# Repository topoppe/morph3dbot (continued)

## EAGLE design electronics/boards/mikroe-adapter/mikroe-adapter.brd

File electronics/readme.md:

# *Morph3DBot*-Platinen

Alle Platinen für das *Morph3DBot* System haben den selben Formfaktor und werden auf die Basisstruktur montiert.
Die Platinen werden untereinander mit einem vierpoligen Kabel verbunden. Über dieses Kabel werden die Platinen mit Strom versorgt und können
miteinander kommunizieren.

Die Kommunikation erfolgt über einen I2C-Bus, die Spannungsversorgung bringt die Batteriespannung an alle Platinen.

Jede Platine hat mindestens 2 Stecker zum verbinden mit anderen Platinen. Dadurch kann die Verkabelung zu den einzelnen Modulen
als Daisy-Chain ausgeführt werden und wird wesentlich vereinfacht.
Bei den meisten Platinen lässt sich die I2C-Adresse entweder per Software oder per DIP-Schalter einstellen.

Bis jetzt gibt es bereits folgende Platinen:
- Stromversorgung: Diese Platine darf und muss genau einmal im System verbaut werden. Hier wird die Stromquelle wie z.B. eine Batterie oder ein Netzteil angeschlossen. Außerdem sind hier die Pull-Up-Widerstände für den I2C-Bus verbaut.
- HUB-Platine: Dient als Verteiler. Hier können bis zu 8 weitere Platinen angeschlossen werden
- AT-Mega-328-Platine: Diese Platine ist mit einem ATMega328p Controller bestückt. Sie kann als "Gehirn" des Systems verwendet werden
- ESP32-Platine: Diese Platine ist mit einem ESP32-Wroom-Modul bestückt. Auch sie kann als "Gehirn" verwendet werden, besitzt aber auch WLAN und Bluetooth Schnittstellen
- Taster-Platine: Sie besitzt 5 Taster um eingaben ins System zu ermöglichen
- Ultrasonic-Platine: Hier kann ein 4-poliger Ultraschall Sensor angeschlossen werden
- Motor-und-Servo-Platine: An dieser Platine können 8 Servos sowie 2 Gleichstrommotoren angeschlossen werden
- Servo-Platine: Wie die Motor-und-Servo-Platine, jedoch ohne die Anschlüsse für die Gleichstrommotoren
- Line-Follower-Platine: Mit ihr kann eine Linie auf dem Boden erkannt werden
- Mikroe-Platine: Hier kann ein "Click-Board" von Mikroe.com angeschlossen werden

Zusätzlich gibt es eine Platine mit einem anderen Formfaktor: Die "TT-Motor-Platine". Diese Platine kann direkt auf die aus dem Maker-Bereich bekannten TT-Motoren geklebt werden. Sie besitzt eine I2C-Schnittstelle, einen Motortreiber sowie Eingänge für den Enkoder des Motors. Angeschlossen wird die Platine mit dem selben System wie die restlichen *Morph3DBot* Platinen.

Für die ATMega, die ESP32- sowie für die Platinen mit ATTINY-Controller stehen Templates im Repo bereit. Alle Grundbauteile sind bereits vorhanden, sodass eigene Platinen schnell erstellt werden können.

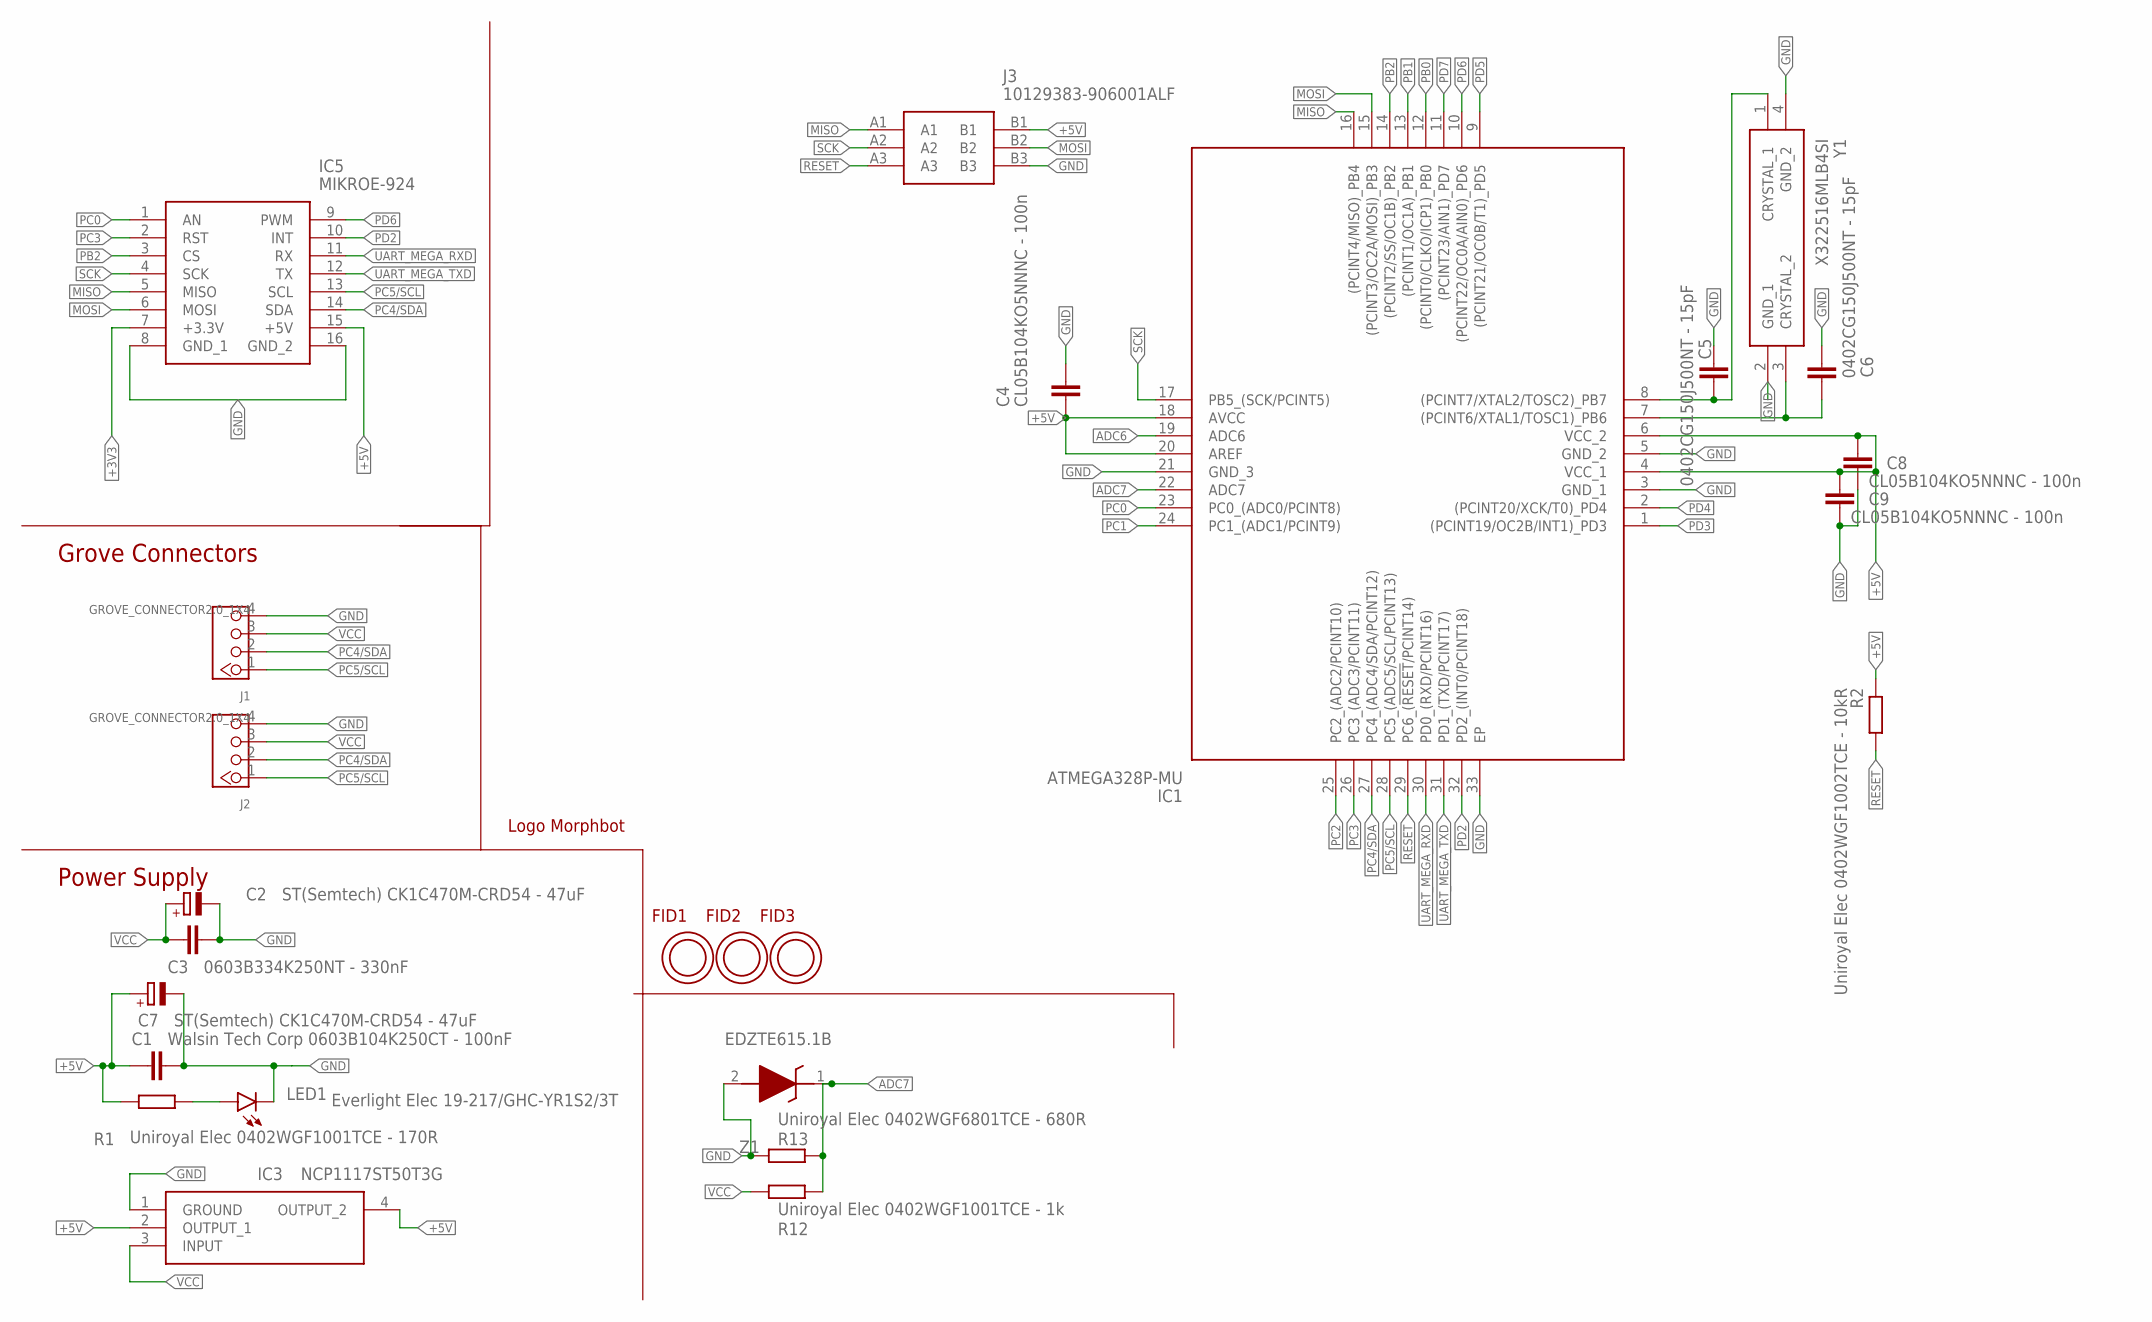
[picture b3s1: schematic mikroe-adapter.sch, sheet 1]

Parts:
C1: Walsin Tech Corp 0603B104K250CT - 100nF; C0603
C2, C7: ST(Semtech) CK1C470M-CRD54 - 47uF; PANASONIC_C
C3: 0603B334K250NT - 330nF; C0603
C4, C8, C9: CL05B104KO5NNNC - 100n; C0402
C5, C6: 0402CG150J500NT - 15pF; C0402
FID1, FID2, FID3: OPEN-PNP-FIDUCIAL
IC1: ATMEGA328P-MU; QFN50P500X500X100-33N
IC3: NCP1117ST50T3G; SOT230P700X180-4N
IC5: MIKROE-924; MIKROE924
J1, J2: GROVE_CONNECTOR2.0_1X4; 2.0_1X4_STRAIGHT
J3: 10129383-906001ALF; 10129383906001ALF
LED1: Everlight Elec 19-217/GHC-YR1S2/3T; CHIPLED_0603
R1: Uniroyal Elec 0402WGF1001TCE - 170R; R0402
R2: Uniroyal Elec 0402WGF1002TCE - 10kR; R0402
R12: Uniroyal Elec 0402WGF1001TCE - 1k; R0402
R13: Uniroyal Elec 0402WGF6801TCE - 680R; R0402
U$1: LOGO_MORPHBOT5MM; LOGO_MORPHBOT
Y1: X322516MLB4SI
Z1: EDZTE615.1B; EMD2

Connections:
+3V3: IC5.7 (+3.3V); also elsewhere on the board
+5V: C1.1, C4.1, C7.+, C8.2, C9.2, IC1.4 (VCC_1), IC1.6 (VCC_2), IC1.18 (AVCC), IC1.20 (AREF), IC3.2 (OUTPUT_1), IC3.4 (OUTPUT_2), IC5.15 (+5V), J3.B1, R1.2, R2.2; also elsewhere on the board
ADC6: IC1.19 (ADC6)
ADC7: IC1.22 (ADC7), R12.1, R13.2, Z1.1 (K)
GND: C1.2, C2.-, C3.1, C4.2, C5.1, C6.1, C7.-, C8.1, C9.1, IC1.3 (GND_1), IC1.5 (GND_2), IC1.21 (GND_3), IC1.33 (EP), IC3.1 (GROUND), IC5.8 (GND_1), IC5.16 (GND_2), J1.4, J2.4, J3.B3, LED1.C, R13.1, Y1.2 (GND_1), Y1.4 (GND_2), Z1.2 (A); also elsewhere on the board
MISO: IC1.16 ((PCINT4/MISO)_PB4), IC5.5 (MISO), J3.A1
MOSI: IC1.15 ((PCINT3/OC2A/MOSI)_PB3), IC5.6 (MOSI), J3.B2
unnamed: LED1.A, R1.1
unnamed: C5.2, IC1.8 ((PCINT7/XTAL2/TOSC2)_PB7), Y1.1 (CRYSTAL_1)
unnamed: C6.2, IC1.7 ((PCINT6/XTAL1/TOSC1)_PB6), Y1.3 (CRYSTAL_2)
PB0: IC1.12 ((PCINT0/CLKO/ICP1)_PB0)
PB1: IC1.13 ((PCINT1/OC1A)_PB1)
PB2: IC1.14 ((PCINT2/SS/OC1B)_PB2), IC5.3 (CS)
PC0: IC1.23 (PC0_(ADC0/PCINT8)), IC5.1 (AN)
PC1: IC1.24 (PC1_(ADC1/PCINT9))
PC2: IC1.25 (PC2_(ADC2/PCINT10))
PC3: IC1.26 (PC3_(ADC3/PCINT11)), IC5.2 (RST)
PC4/SDA: IC1.27 (PC4_(ADC4/SDA/PCINT12)), IC5.14 (SDA), J1.2, J2.2
PC5/SCL: IC1.28 (PC5_(ADC5/SCL/PCINT13)), IC5.13 (SCL), J1.1, J2.1
PD2: IC1.32 (PD2_(INT0/PCINT18)), IC5.10 (INT)
PD3: IC1.1 ((PCINT19/OC2B/INT1)_PD3)
PD4: IC1.2 ((PCINT20/XCK/T0)_PD4)
PD5: IC1.9 ((PCINT21/OC0B/T1)_PD5)
PD6: IC1.10 ((PCINT22/OC0A/AIN0)_PD6), IC5.9 (PWM)
PD7: IC1.11 ((PCINT23/AIN1)_PD7)
RESET: IC1.29 (PC6_(!RESET!/PCINT14)), J3.A3, R2.1; also elsewhere on the board
SCK: IC1.17 (PB5_(SCK/PCINT5)), IC5.4 (SCK), J3.A2
UART_MEGA_RXD: IC1.30 (PD0_(RXD/PCINT16)), IC5.11 (RX); also elsewhere on the board
UART_MEGA_TXD: IC1.31 (PD1_(TXD/PCINT17)), IC5.12 (TX); also elsewhere on the board
VCC: C2.+, C3.2, IC3.3 (INPUT), J1.3, J2.3, R12.2; also elsewhere on the board

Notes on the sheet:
Power Supply
Grove Connectors

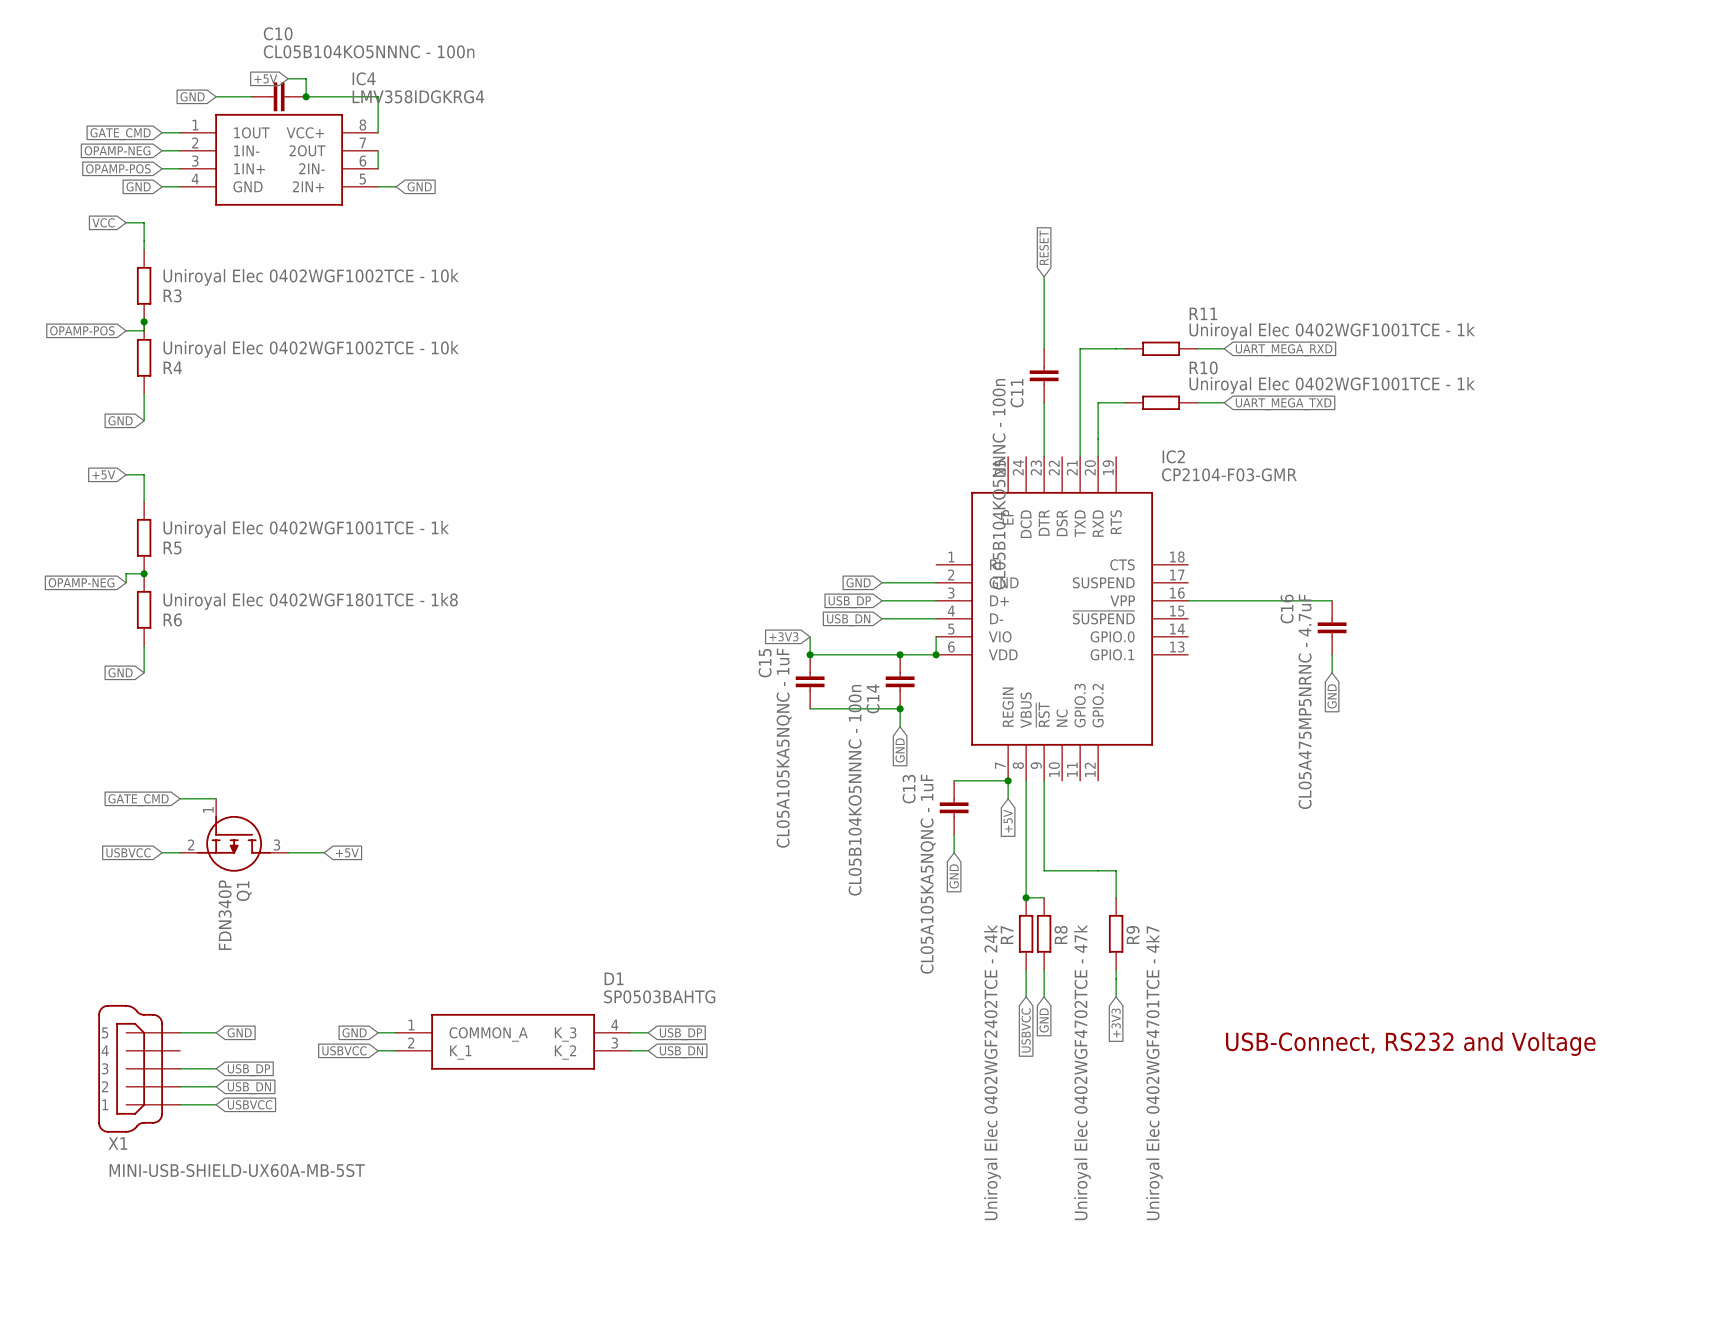
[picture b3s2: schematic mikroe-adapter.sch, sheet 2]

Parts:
C10, C11, C14: CL05B104KO5NNNC - 100n; C0402
C13, C15: CL05A105KA5NQNC - 1uF; C0402
C16: CL05A475MP5NRNC - 4.7uF; C0402
D1: SP0503BAHTG
IC2: CP2104-F03-GMR; QFN50P400X400X80-25N
IC4: LMV358IDGKRG4; SOP65P490X110-8N
Q1: FDN340P; SOT95P237X112-3N
R3, R4: Uniroyal Elec 0402WGF1002TCE - 10k; R0402
R5, R10, R11: Uniroyal Elec 0402WGF1001TCE - 1k; R0402
R6: Uniroyal Elec 0402WGF1801TCE - 1k8; R0402
R7: Uniroyal Elec 0402WGF2402TCE - 24k; R0402
R8: Uniroyal Elec 0402WGF4702TCE - 47k; R0402
R9: Uniroyal Elec 0402WGF4701TCE - 4k7; R0402
X1: MINI-USB-SHIELD-UX60A-MB-5ST; UX60A-MB-5ST

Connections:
+3V3: C14.2, C15.2, IC2.5 (VIO), IC2.6 (VDD), R9.2; also elsewhere on the board
+5V: C10.2, C13.2, IC2.7 (REGIN), IC4.8 (VCC+), Q1.3 (D), R5.1; also elsewhere on the board
DTR: C11.1, IC2.23 (DTR)
GATE_CMD: IC4.1 (1OUT), Q1.1 (G)
GND: C10.1, C13.1, C14.1, C15.1, C16.1, D1.1 (COMMON_A), IC2.2 (GND), IC4.4 (GND), IC4.5 (2IN+), R4.2, R6.2, R8.2, X1.5; also elsewhere on the board
unnamed: IC4.6 (2IN-), IC4.7 (2OUT)
unnamed: IC2.8 (VBUS), R7.1, R8.1
unnamed: IC2.9 (!RST), R9.1
unnamed: C16.2, IC2.16 (VPP)
unnamed: IC2.21 (TXD), R11.1
unnamed: IC2.20 (RXD), R10.1
OPAMP-NEG: IC4.2 (1IN-), R5.2, R6.1
OPAMP-POS: IC4.3 (1IN+), R3.2, R4.1
RESET: C11.2; also elsewhere on the board
UART_MEGA_RXD: R11.2; also elsewhere on the board
UART_MEGA_TXD: R10.2; also elsewhere on the board
USBVCC: D1.2 (K_1), Q1.2 (S), R7.2, X1.1
USB_DN: D1.3 (K_2), IC2.4 (D-), X1.2
USB_DP: D1.4 (K_3), IC2.3 (D+), X1.3
VCC: R3.1; also elsewhere on the board

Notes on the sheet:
USB-Connect, RS232 and Voltage

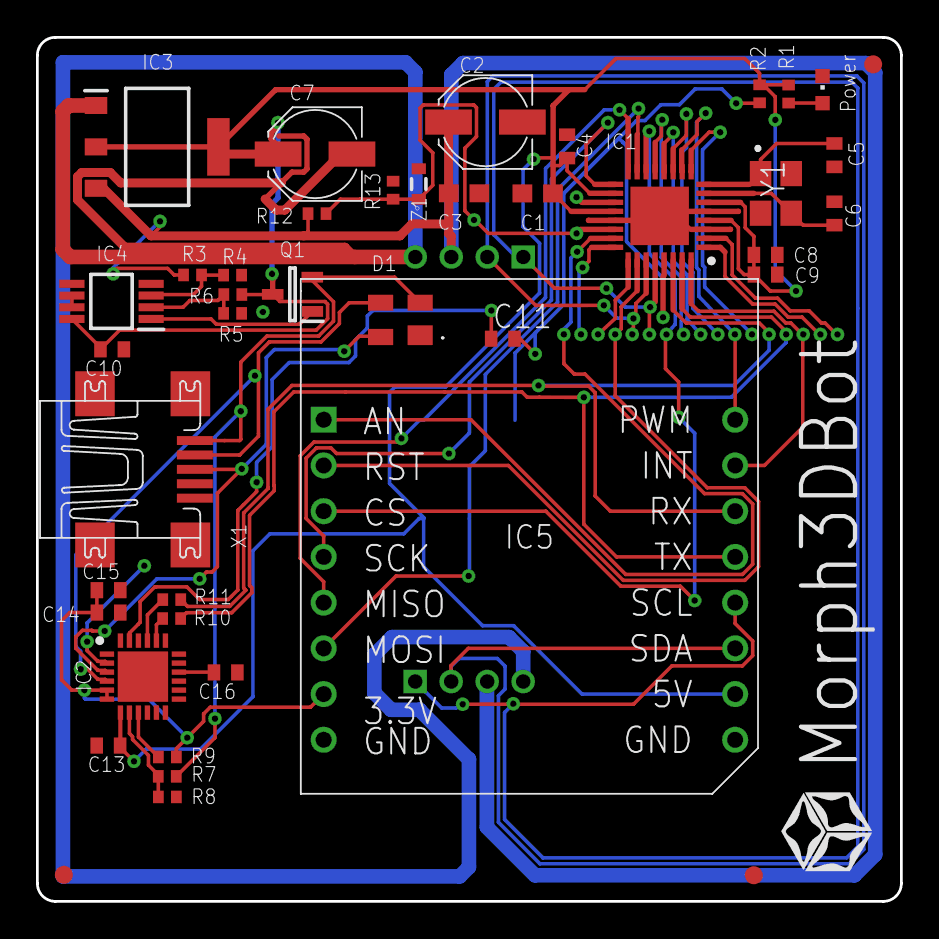
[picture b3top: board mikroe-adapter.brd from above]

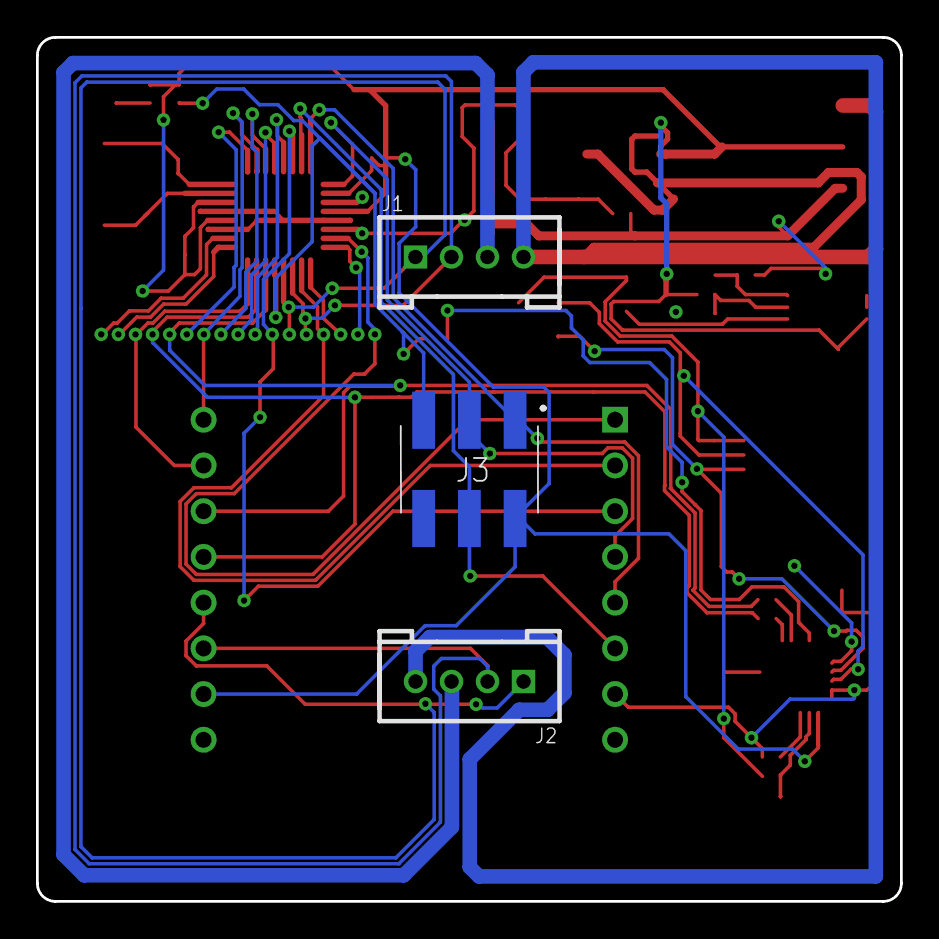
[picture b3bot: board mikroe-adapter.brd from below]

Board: 2 copper layers, 48.0 x 48.0 mm, 46 parts (3 on the bottom side), 34 nets.

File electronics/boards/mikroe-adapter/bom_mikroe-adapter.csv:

"Qty";"Value";"Device";"Package";"Parts";"Description";"ARROW_PART_NUMBER";"ARROW_PRICE-STOCK";"DESCRIPTION";"HEIGHT";"MANUFACTURER_NAME";"MANUFACTURER_PART_NUMBER";"MF";"MOUSER_PART_NUMBER";"MOUSER_PRICE-STOCK";"MPN";"OC_FARNELL";"OC_NEWARK";"POPULARITY";"SPICEPREFIX";
"2";"0402CG150J500NT - 15pF";"C-EUC0402";"C0402";"C5, C6";"CAPACITOR, European symbol";"";"";"";"";"";"";"";"";"";"";"";"";"18";"C";
"1";"0603B334K250NT - 330nF";"C-EUC0603";"C0603";"C3";"CAPACITOR, European symbol";"";"";"";"";"";"";"";"";"";"";"";"";"73";"C";
"1";"10129383-906001ALF";"10129383-906001ALF";"10129383906001ALF";"J3";"Headers & Wire Housings ECONOSTIK HEADER DR VT SMT 2X3";"10129383-906001ALF";"https://www.arrow.com/en/products/10129383-906001alf/amphenol-fci";"Headers & Wire Housings ECONOSTIK HEADER DR VT SMT 2X3";"8.58mm";"Amphenol";"10129383-906001ALF";"";"649-1012938390601ALF";"https://www.mouser.co.uk/ProductDetail/Amphenol-FCI/10129383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";"";"";"";"";"";
"1";"ATMEGA328P-MU";"ATMEGA328P-MU";"QFN50P500X500X100-33N";"IC1";"ATMEGA328P-MU, 8 bit AVR Microcontroller 20MHz 1, 32kb Flash, 2kb RAM, I2C SPI 32-Pin MLF";"ATMEGA328P-MU";"https://www.arrow.com/en/products/atmega328p-mu/microchip-te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";"ATMEGA328P-MU, 8 bit AVR Microcontroller 20MHz 1, 32kb Flash, 2kb RAM, I2C SPI 32-Pin MLF";"1mm";"Microchip";"ATMEGA328P-MU";"";"556-ATMEGA328P-MU";"https://www.mouser.co.uk/ProductDetail/Microchip-Technology-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";"";"";"";"";"";
"2";"CL05A105KA5NQNC - 1uF";"C-EUC0402";"C0402";"C13, C15";"CAPACITOR, European symbol";"";"";"";"";"";"";"";"";"";"";"";"";"18";"C";
"1";"CL05A475MP5NRNC - 4.7uF";"C-EUC0402";"C0402";"C16";"CAPACITOR, European symbol";"";"";"";"";"";"";"";"";"";"";"";"";"18";"C";
"6";"CL05B104KO5NNNC - 100n";"C-EUC0402";"C0402";"C4, C8, C9, C10, C11, C14";"CAPACITOR, European symbol";"";"";"";"";"";"";"";"";"";"";"";"";"18";"C";
"1";"CP2104-F03-GMR";"CP2104-F03-GMR";"QFN50P400X400X80-25N";"IC2";"USB-to-UART 1-CH 576byte FIFO 3.3V Automotive 24-Pin QFN EP T/R";"CP2104-F03-GMR";"https://www.arrow.com/en/products/cp2104-f03-gmr/silicon-labs";"USB-to-UART 1-CH 576byte FIFO 3.3V Automotive 24-Pin QFN EP T/R";"0.8mm";"Silicon Labs";"CP2104-F03-GMR";"";"634-CP2104-F03-GMR";"https://www.mouser.co.uk/ProductDetail/Silicon-Labs/CP2104-F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";"";"";"";"";"";
"1";"EDZTE615.1B";"EDZTE615.1B";"EMD2";"Z1";"ROHM EDZTE615.1B Zener Diode, 5.1V 2% 0.1 W SMT 2-Pin EMD";"";"";"ROHM EDZTE615.1B Zener Diode, 5.1V 2% 0.1 W SMT 2-Pin EMD";"mm";"ROHM Semiconductor";"EDZTE615.1B";"";"755-EDZTE615.1B";"https://www.mouser.co.uk/ProductDetail/ROHM-Semiconductor/ED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";"";"";"";"";"";
"1";"Everlight Elec 19-217/GHC-YR1S2/3T";"LEDCHIPLED_0603";"CHIPLED_0603";"LED1";"LED";"";"";"";"";"";"";"";"";"";"";"";"";"28";"";
"1";"FDN340P";"FDN340P";"SOT95P237X112-3N";"Q1";"Trans MOSFET P-CH 20V 2A 3-Pin SuperSOT";"FDN340P";"https://www.arrow.com/en/products/fdn340p/on-semiconductor";"Trans MOSFET P-CH 20V 2A 3-Pin SuperSOT";"1.12mm";"ON Semiconductor";"FDN340P";"";"512-FDN340P";"https://www.mouser.co.uk/ProductDetail/ON-Semiconductor-Fair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";"";"";"";"";"";
"2";"GROVE_CONNECTOR2.0_1X4";"GROVE_CONNECTOR2.0_1X4";"2.0_1X4_STRAIGHT";"J1, J2";"Seeedstudio Grove-Connector:";"";"";"";"";"";"";"";"";"";"";"";"";"";"";
"1";"LMV358IDGKRG4";"LMV358IDGKRG4";"SOP65P490X110-8N";"IC4";"Operational Amplifiers - Op Amps Dual Low-Voltage Rail-to-Rail Out";"LMV358IDGKRG4";"https://www.arrow.com/en/products/lmv358idgkrg4/texas-instruments";"Operational Amplifiers - Op Amps Dual Low-Voltage Rail-to-Rail Out";"1.1mm";"Texas Instruments";"LMV358IDGKRG4";"";"595-LMV358IDGKRG4";"https://www.mouser.co.uk/ProductDetail/Texas-Instruments/LMV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";"";"";"";"";"";
"1";"LOGO_MORPHBOT5MM";"LOGO_MORPHBOT5MM";"LOGO_MORPHBOT";"U$1";"";"";"";"";"";"";"";"";"";"";"";"";"";"";"";
"1";"MIKROE-924";"MIKROE-924";"MIKROE924";"IC5";"microSD click mikroBUS";"";"";"microSD click mikroBUS";"5mm";"MIKROELEKTRONIKA";"MIKROE-924";"";"932-MIKROE-924";"https://www.mouser.com/Search/Refine.aspx?Keyword=932-MIKROE-924";"";"";"";"";"";
"1";"MINI-USB-SHIELD-UX60A-MB-5ST";"MINI-USB-SHIELD-UX60A-MB-5ST";"UX60A-MB-5ST";"X1";"MINI USB Connector";"";"";"";"";"";"";"";"";"";"";"unknown";"unknown";"0";"";
"1";"NCP1117ST50T3G";"NCP1117ST50T3G";"SOT230P700X180-4N";"IC3";"ON SEMICONDUCTOR - NCP1117ST50T3G - LDO, REG, 20VIN, 1A, 5V, 1%, SOT223-3";"NCP1117ST50T3G";"https://www.arrow.com/en/products/ncp1117st50t3g/on-semiconductor";"ON SEMICONDUCTOR - NCP1117ST50T3G - LDO, REG, 20VIN, 1A, 5V, 1%, SOT223-3";"1.8mm";"ON Semiconductor";"NCP1117ST50T3G";"";"863-NCP1117ST50T3G";"https://www.mouser.co.uk/ProductDetail/ON-Semiconductor/NCP1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";"";"";"";"";"";
"3";"OPEN-PNP-FIDUCIAL";"OPEN-PNP-FIDUCIAL";"OPEN-PNP-FIDUCIAL";"FID1, FID2, FID3";"";"";"";"";"";"";"";"";"";"";"";"";"";"";"";
"1";"SP0503BAHTG";"SP0503BAHTG";"SP0503BAHTG";"D1";"ESD Suppressors / TVS Diodes TVS AVAL DIODE SMT";"SP0503BAHTG";"https://www.arrow.com/en/products/sp0503bahtg/littelfuse";"ESD Suppressors / TVS Diodes TVS AVAL DIODE SMT";"1.22mm";"LITTELFUSE";"SP0503BAHTG";"";"576-SP0503BAHTG";"https://www.mouser.co.uk/ProductDetail/Littelfuse/SP0503BAHT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";"";"";"";"";"";
"2";"ST(Semtech) CK1C470M-CRD54 - 47uF";"CPOL-EUC";"PANASONIC_C";"C2, C7";"POLARIZED CAPACITOR, European symbol";"";"";"";"";"";"";"";"";"";"";"";"";"4";"C";
"1";"Uniroyal Elec 0402WGF1001TCE - 170R";"R-EU_R0402";"R0402";"R1";"RESISTOR, European symbol";"";"";"";"";"";"";"";"";"";"";"";"";"0";"R";
"4";"Uniroyal Elec 0402WGF1001TCE - 1k";"R-EU_R0402";"R0402";"R5, R10, R11, R12";"RESISTOR, European symbol";"";"";"";"";"";"";"";"";"";"";"";"";"0";"R";
"2";"Uniroyal Elec 0402WGF1002TCE - 10k";"R-EU_R0402";"R0402";"R3, R4";"RESISTOR, European symbol";"";"";"";"";"";"";"";"";"";"";"";"";"0";"R";
"1";"Uniroyal Elec 0402WGF1002TCE - 10kR";"R-EU_R0402";"R0402";"R2";"RESISTOR, European symbol";"";"";"";"";"";"";"";"";"";"";"";"";"0";"R";
"1";"Uniroyal Elec 0402WGF1801TCE - 1k8";"R-EU_R0402";"R0402";"R6";"RESISTOR, European symbol";"";"";"";"";"";"";"";"";"";"";"";"";"0";"R";
"1";"Uniroyal Elec 0402WGF2402TCE - 24k";"R-EU_R0402";"R0402";"R7";"RESISTOR, European symbol";"";"";"";"";"";"";"";"";"";"";"";"";"0";"R";
"1";"Uniroyal Elec 0402WGF4701TCE - 4k7";"R-EU_R0402";"R0402";"R9";"RESISTOR, European symbol";"";"";"";"";"";"";"";"";"";"";"";"";"0";"R";
"1";"Uniroyal Elec 0402WGF4702TCE - 47k";"R-EU_R0402";"R0402";"R8";"RESISTOR, European symbol";"";"";"";"";"";"";"";"";"";"";"";"";"0";"R";
"1";"Uniroyal Elec 0402WGF6801TCE - 680R";"R-EU_R0402";"R0402";"R13";"RESISTOR, European symbol";"";"";"";"";"";"";"";"";"";"";"";"";"0";"R";
"1";"Walsin Tech Corp 0603B104K250CT - 100nF";"C-EUC0603";"C0603";"C1";"CAPACITOR, European symbol";"";"";"";"";"";"";"";"";"";"";"";"";"73";"C";
"1";"X322516MLB4SI";"X322516MLB4SI";"X322516MLB4SI";"Y1";"Crystal";"";"";"Crystal";"0.8mm";"Yangxing Tech";"X322516MLB4SI";"";"";"";"";"";"";"";"";

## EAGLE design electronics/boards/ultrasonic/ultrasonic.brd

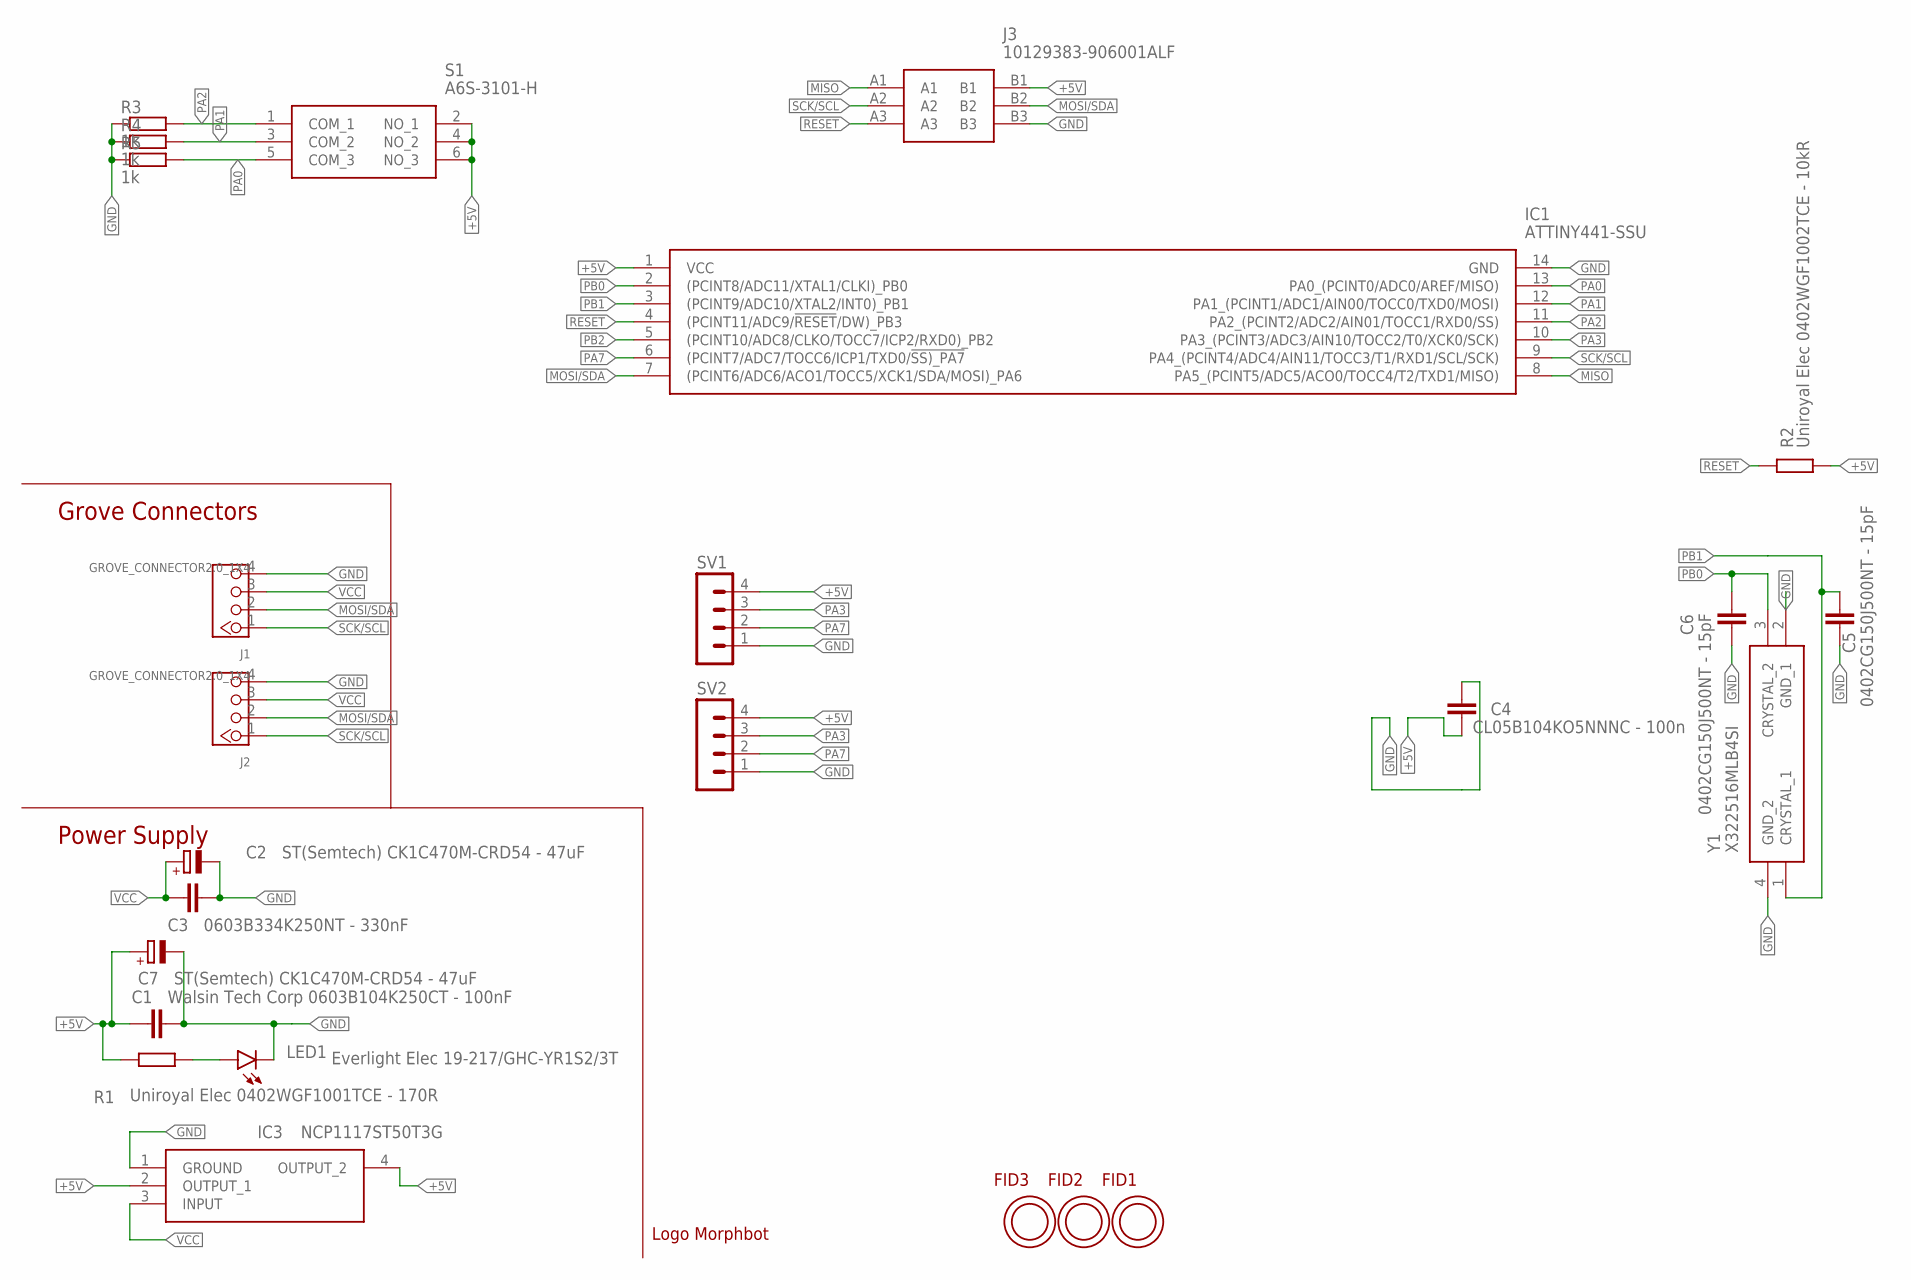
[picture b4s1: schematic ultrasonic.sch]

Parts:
C1: Walsin Tech Corp 0603B104K250CT - 100nF; C0603
C2, C7: ST(Semtech) CK1C470M-CRD54 - 47uF; PANASONIC_C
C3: 0603B334K250NT - 330nF; C0603
C4: CL05B104KO5NNNC - 100n; C0402
C5, C6: 0402CG150J500NT - 15pF; C0402
FID1, FID2, FID3: OPEN-PNP-FIDUCIAL
IC1: ATTINY441-SSU; SOIC127P600X175-14N
IC3: NCP1117ST50T3G; SOT230P700X180-4N
J1, J2: GROVE_CONNECTOR2.0_1X4; 2.0_1X4_STRAIGHT
J3: 10129383-906001ALF; 10129383906001ALF
LED1: Everlight Elec 19-217/GHC-YR1S2/3T; CHIPLED_0603
R1: Uniroyal Elec 0402WGF1001TCE - 170R; R0402
R2: Uniroyal Elec 0402WGF1002TCE - 10kR; R0402
R3, R4, R5: 1k; R0402
S1: A6S-3101-H; A6S3104H
SV1, SV2: MA04-1
U$1: LOGO_MORPHBOT5MM; LOGO_MORPHBOT
Y1: X322516MLB4SI

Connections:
+5V: C1.1, C4.1, C7.+, IC1.1 (VCC), IC3.2 (OUTPUT_1), IC3.4 (OUTPUT_2), J3.B1, R1.2, R2.2, S1.2 (NO_1), S1.4 (NO_2), S1.6 (NO_3), SV1.4, SV2.4
GND: C1.2, C2.-, C3.1, C4.2, C5.1, C6.1, C7.-, IC1.14 (GND), IC3.1 (GROUND), J1.4, J2.4, J3.B3, LED1.C, R3.1, R4.1, R5.1, SV1.1, SV2.1, Y1.2 (GND_1), Y1.4 (GND_2)
MISO: IC1.8 (PA5_(PCINT5/ADC5/ACO0/TOCC4/T2/TXD1/MIS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), J3.A1
MOSI/SDA: IC1.7 ((PCINT6/ADC6/ACO1/TOCC5/XCK1/SDA/MOSI)_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), J1.2, J2.2, J3.B2
unnamed: LED1.A, R1.1
PA0: IC1.13 (PA0_(PCINT0/ADC0/AREF/MISO)), R5.2, S1.5 (COM_3)
PA1: IC1.12 (PA1_(PCINT1/ADC1/AIN00/TOCC0/TXD0/MOSI)), R4.2, S1.3 (COM_2)
PA2: IC1.11 (PA2_(PCINT2/ADC2/AIN01/TOCC1/RXD0/SS)), R3.2, S1.1 (COM_1)
PA3: IC1.10 (PA3_(PCINT3/ADC3/AIN10/TOCC2/T0/XCK0/SC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), SV1.3, SV2.3
PA7: IC1.6 ((PCINT7/ADC7/TOCC6/ICP1/TXD0/!SS)_PA7), SV1.2, SV2.2
PB0: C6.2, IC1.2 ((PCINT8/ADC11/XTAL1/CLKI)_PB0), Y1.3 (CRYSTAL_2)
PB1: C5.2, IC1.3 ((PCINT9/ADC10/XTAL2/INT0)_PB1), Y1.1 (CRYSTAL_1)
PB2: IC1.5 ((PCINT10/ADC8/CLKO/TOCC7/ICP2/RXD0)_PB2)
RESET: IC1.4 ((PCINT11/ADC9/!RESET!/DW)_PB3), J3.A3, R2.1
SCK/SCL: IC1.9 (PA4_(PCINT4/ADC4/AIN11/TOCC3/T1/RXD1/SC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), J1.1, J2.1, J3.A2
VCC: C2.+, C3.2, IC3.3 (INPUT), J1.3, J2.3

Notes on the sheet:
Power Supply
Grove Connectors

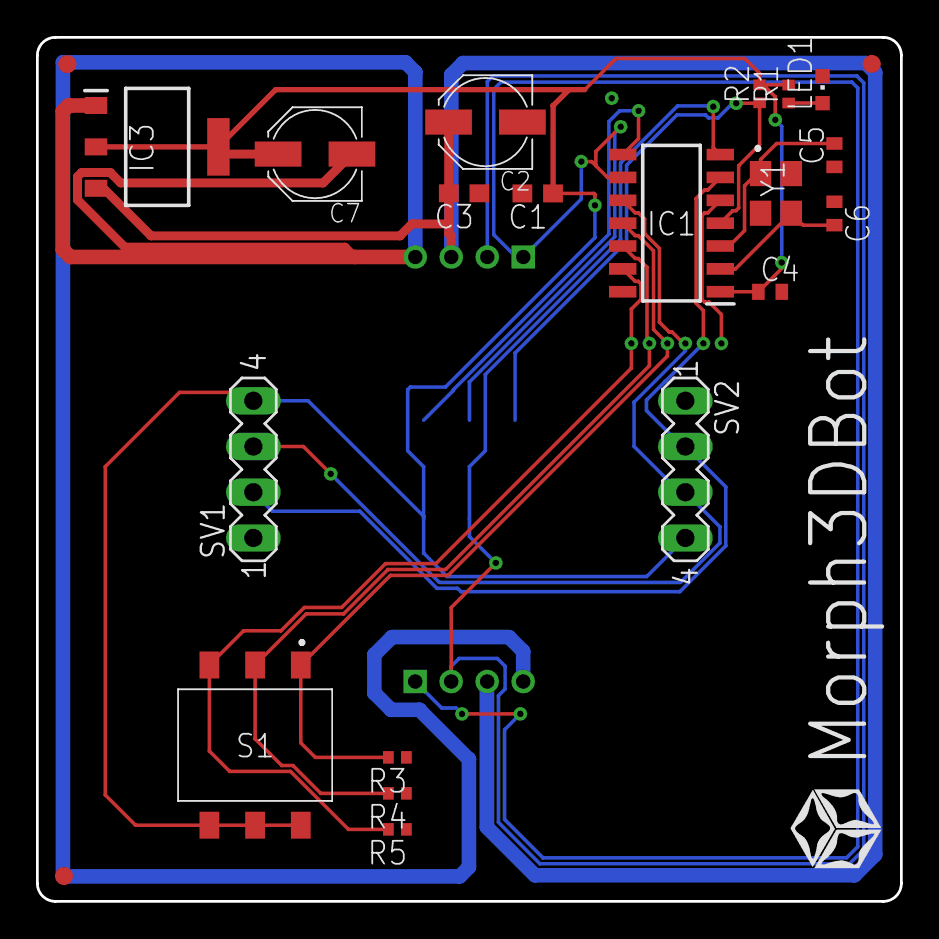
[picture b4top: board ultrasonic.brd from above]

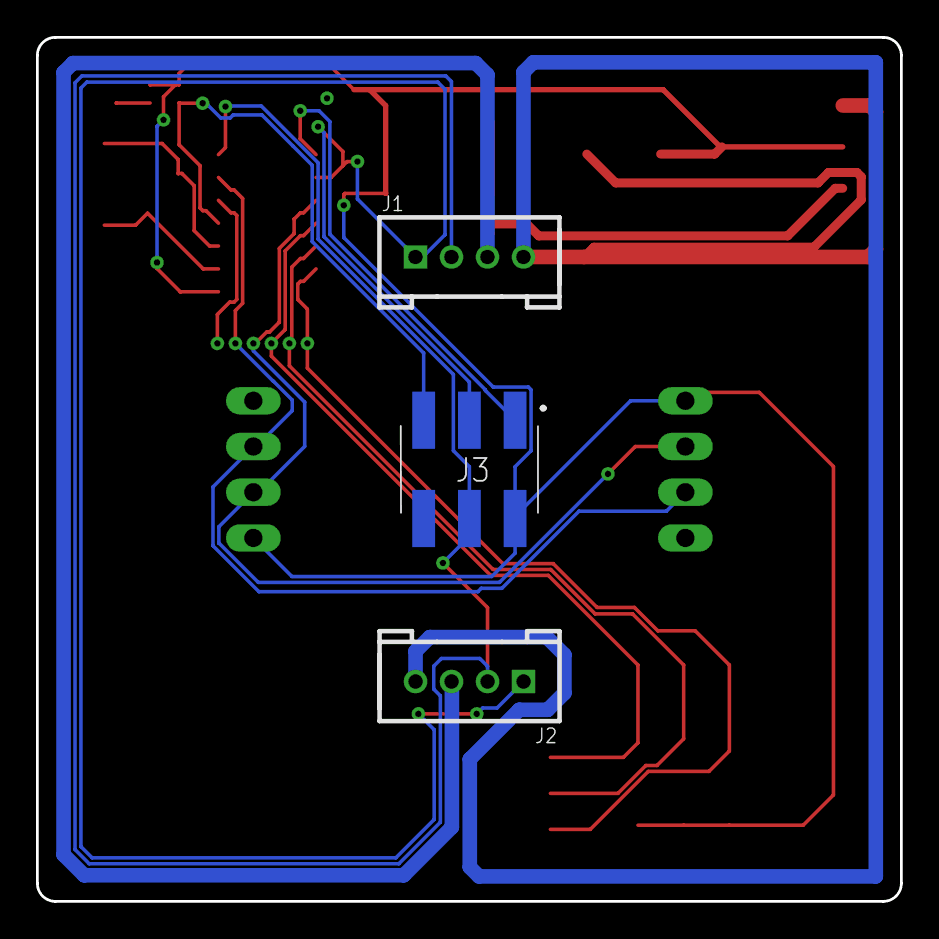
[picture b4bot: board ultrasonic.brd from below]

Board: 2 copper layers, 48.0 x 48.0 mm, 26 parts (3 on the bottom side), 15 nets.
